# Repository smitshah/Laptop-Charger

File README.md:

# Laptop-Charger

**Problem statement:**

Design a circuit of Laptop Charger which will take input of 13V DC and gives output of 19V DC.

**MATERIALS USED:**
* LM3254
* 4.4k ohm Resistor
* 2.4k ohm Resistor
* 12k ohm Resistor
* 0.04 ohm Resistor
* 2.7 ohm Resistor
* 2.2k ohm Resistor
* 1M ohm Resistor
* 1k ohm Resistor
* 470 ohm Resistor
* 1.8k ohm Resistor
* 20V, 1000µF Capacitors
* 20V, 10µF Capacitors
* 0.1µF Capacitors
* 0.022µF Capacitors
* 1000pF Capacitors
* 25V, 4.7µF Capacitors
* 1N4148 Diode
* SB580 Diode
* BC547 Transistor
* BUZ78 Transistor
* Connectors
* 100µH Inductor
* 10A Fuse
* Connecting wires
* Power supply
* General Purpose Board
* Copper Clad

he schematic and footprint allocation for our circuit is as below:

KiCAD Schematic:

Footprint Allocation to the Schematic:

**KiCAD GERBER FILE GENERATION:**

After footprint allocation, we move to net-list generation which is the process of importing the footprint allocation onto a virtual PCB. Here, we can place the components in the most effective manner onto our PCB board and can hence visualise how our final PCB structure look like by viewing the virtual 3D model. We can then complete the tracking and override them to make it most effective. We can choose the layers of the PCB we need in our final output and create a gerber file of it. We can save the gerber file in PDF format also. This PDF file is collection of all the layers of the PCB that we choose to have. Out of all of these files, the most important one is B.Cu file. It is the back copper tracking between all these components of our final PCB.

Final PCB Layout:

The 3-D view of front-side and back-side our PCB is as below:

**TONER TRANSFER:**

Toner transfer is the process by which we create our actual track of our circuit. We take the B.Cu file (PDF Format) and get it printed on a photo paper with a good quality ink. After the printout is taken, it is placed upside down on the copper clad and is taped down to it. We then cover it with a piece of cloth and heat it with the help of Iron. We press it down and run the iron over it until the ink is transferred onto the copper clad from the paper. This process of transferring ink from photo paper onto copper clad is called toner transfer.

**ETCHING:**

Etching is a method used for the production of the PCBs where acid is used to remove unwanted copper from a prefabricated laminate. This is done by applying a temporary mask (in our case, ink), that protects part of the laminate from the acid and leaves the desired copper layer untouched. The etching solution used by us is ferric chloride. Thus, we dip the PCB in boiling FeCl3 solution and wait until the excess copper is dissolved off and only our tracks of circuit remains. After this is done, we take out the board and clean it using water.

**DRILLING AND SOLDERING:**

After cleaning the board, we proceed to drill the board using a PCB drilling machine. We make holes of diameter approximately 1mm. Holes are made wherever components have to be placed. After all the holes are drilled, we proceed to place the components in their respective slots following the PCB layout. Once the components are placed, we solder them so that they stay in place and the connections are complete. We also solder other wires where external connections are required. After soldering, we clean our PCB with IP(Iso-propyl Alcohol) so that the residue of solder is removed. Now our circuit is ready to use. 

Now, we provide the trigger pulse to the input terminal of our circuit and check the operation of the buzzer. If all the above process are carried out in the correct manner, then our buzzer should buzz with the appropriate time intervals.

Actual PCB *(Circuit on General Purpose Board)*:

Actual PCB *(Circuit on Copper Clad)*:

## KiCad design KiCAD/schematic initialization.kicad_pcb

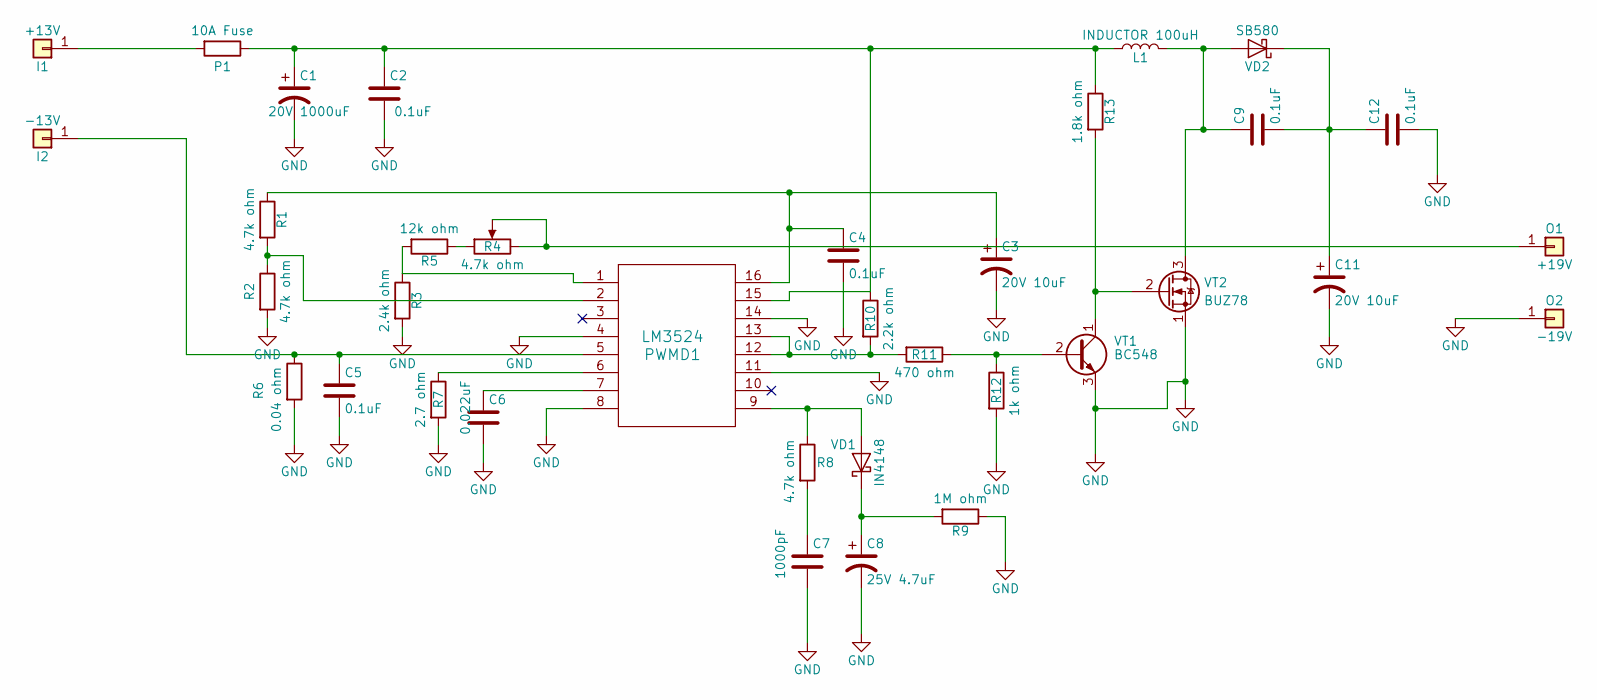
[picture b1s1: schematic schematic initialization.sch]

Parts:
C1: 20V 1000uF; CP_Radial_D10.0mm_P5.00mm
C2, C4, C5, C9, C12: 0.1uF; C_Disc_D3.0mm_W2.0mm_P2.50mm
C3, C11: 20V 10uF; CP_Radial_D4.0mm_P2.00mm
C6: 0.022uF; C_Disc_D6.0mm_W2.5mm_P5.00mm
C7: 1000pF; C_Disc_D4.3mm_W1.9mm_P5.00mm
C8: 25V 4.7uF; CP_Radial_D5.0mm_P2.50mm
I1: +13V; Socket_Strip_Angled_1x01_Pitch2.54mm
I2: -13V; Socket_Strip_Angled_1x01_Pitch2.54mm
L1: INDUCTOR 100uH; L_Axial_L26.0mm_D9.0mm_P30.48mm_Horizontal_Fastron_77A
O1: +19V; Socket_Strip_Angled_1x01_Pitch2.54mm
O2: -19V; Socket_Strip_Angled_1x01_Pitch2.54mm
P1: 10A Fuse; R_Axial_Power_L25.0mm_W9.0mm_P27.94mm
PWMD1: LM3524; DIL16
R1, R2: 4.7k ohm; R_Axial_DIN0207_L6.3mm_D2.5mm_P15.24mm_Horizontal
R3: 2.4k ohm; R_Axial_DIN0207_L6.3mm_D2.5mm_P15.24mm_Horizontal
R4: 4.7k ohm; Potentiometer_Omeg_PC16PU_Vertical
R5: 12k ohm; R_Axial_DIN0207_L6.3mm_D2.5mm_P15.24mm_Horizontal
R6: 0.04 ohm; R_Axial_DIN0207_L6.3mm_D2.5mm_P15.24mm_Horizontal
R7: 2.7 ohm; R_Axial_DIN0207_L6.3mm_D2.5mm_P15.24mm_Horizontal
R8: 4.7k ohm; R_Axial_DIN0309_L9.0mm_D3.2mm_P20.32mm_Horizontal
R9: 1M ohm; R_Axial_DIN0207_L6.3mm_D2.5mm_P15.24mm_Horizontal
R10: 2.2k ohm; R_Axial_DIN0207_L6.3mm_D2.5mm_P15.24mm_Horizontal
R11: 470 ohm; R_Axial_DIN0207_L6.3mm_D2.5mm_P15.24mm_Horizontal
R12: 1k ohm; R_Axial_DIN0207_L6.3mm_D2.5mm_P15.24mm_Horizontal
R13: 1.8k ohm; R_Axial_DIN0207_L6.3mm_D2.5mm_P15.24mm_Horizontal
VD1: IN4148; D_DO-35_SOD27_P12.70mm_Horizontal
VD2: SB580; D_DO-201AD_P15.24mm_Horizontal
VT1: BC548; TO-92_Molded_Narrow
VT2: BUZ78; TO-220-3_Vertical

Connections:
GND: C1.2, C2.2, C3.2, C4.2, C5.2, C6.2, C7.2, C8.2, C11.2, C12.2, O2.1, PWMD1.4, PWMD1.8, PWMD1.11, PWMD1.14, R2.2, R3.2, R6.2, R7.2, R9.1, R12.2, VT1.3 (E), VT2.1 (S)
unnamed: C1.1, C2.1, L1.1, P1.1, PWMD1.15, R10.1, R13.1
unnamed: C3.1, C4.1, PWMD1.16, R1.1
unnamed: C5.1, I2.1, PWMD1.5, R6.1
unnamed: C6.1, PWMD1.7
unnamed: C7.1, R8.2
unnamed: C8.1, R9.2, VD1.1 (K)
unnamed: C9.1, L1.2, VD2.2 (A), VT2.3 (D)
unnamed: C9.2, C11.1, C12.1, VD2.1 (K)
unnamed: I1.1, P1.2
unnamed: O1.1, R4.2, R4.3
unnamed: PWMD1.1, R3.1, R5.2
unnamed: PWMD1.2, R1.2, R2.1
unnamed: PWMD1.6, R7.1
unnamed: PWMD1.9, R8.1, VD1.2 (A)
unnamed: PWMD1.12, PWMD1.13, R10.2, R11.2
unnamed: R4.1, R5.1
unnamed: R11.1, R12.1, VT1.2 (B)
unnamed: R13.2, VT1.1 (C), VT2.2 (G)

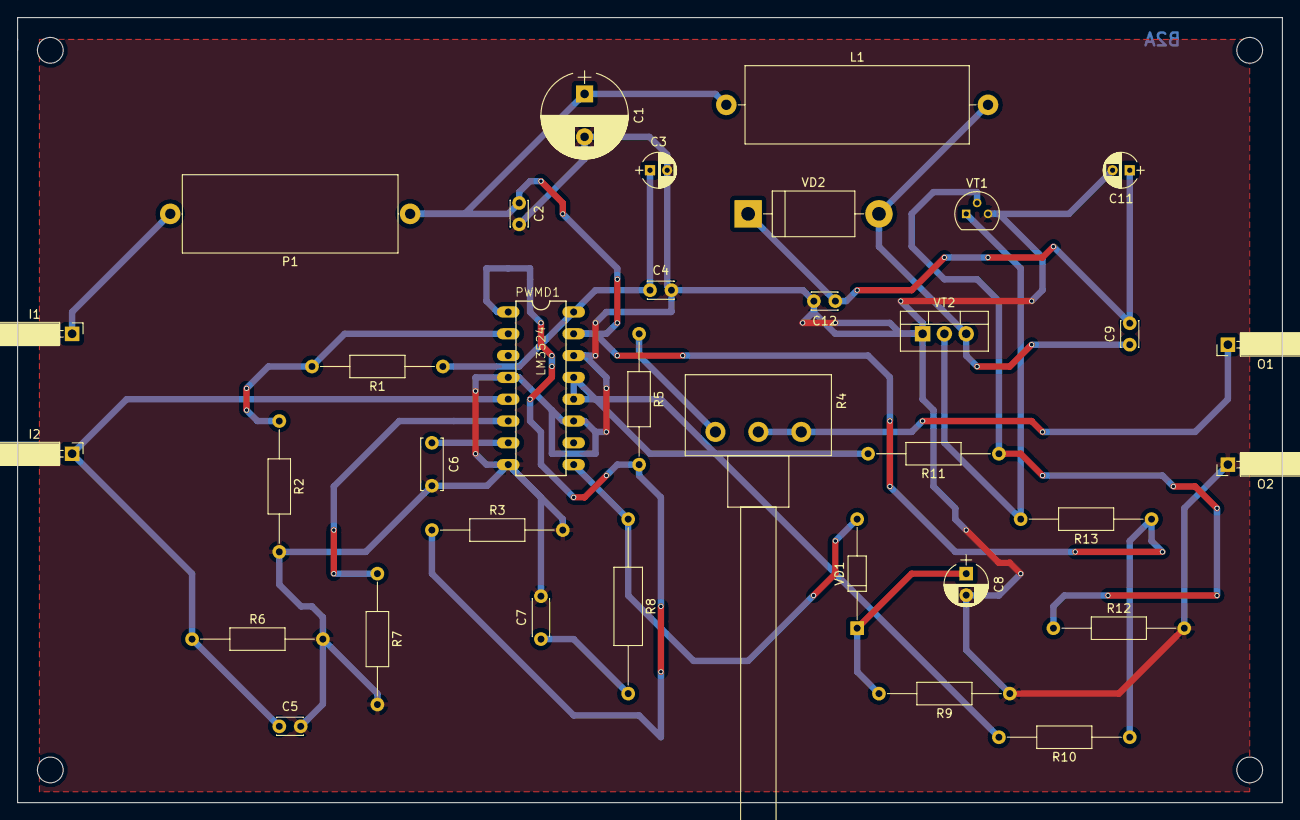
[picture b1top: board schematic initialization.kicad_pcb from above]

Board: 2 copper layers, 147.3 x 91.4 mm, 35 parts (0 on the bottom side), 19 nets.
